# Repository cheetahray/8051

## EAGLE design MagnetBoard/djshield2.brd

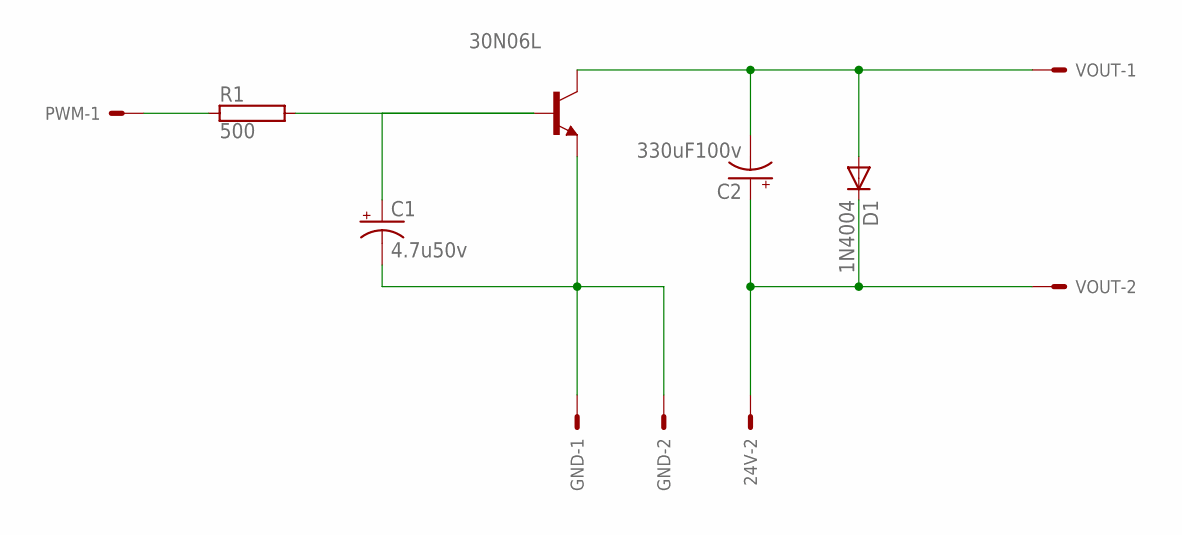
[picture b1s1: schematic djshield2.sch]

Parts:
24V: 87758-0216
30N06L: -NPN-TO126; TO126
C1: 4.7u50v; E1,8-4
C2: 330uF100v; E35-18
D1: 1N4004; DO41-10
GND: 87758-0216
PWM: 87758-0216
R1: 500; RS1/4
VOUT: 87758-0216

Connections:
unnamed: 30N06L.1 (E), C1.-, GND.1, GND.2
unnamed: 30N06L.2 (C), C2.-, D1.A, VOUT.1
unnamed: 24V.2, C2.+, D1.C, VOUT.2
unnamed: 30N06L.3 (B), C1.+, R1.2
unnamed: PWM.1, R1.1

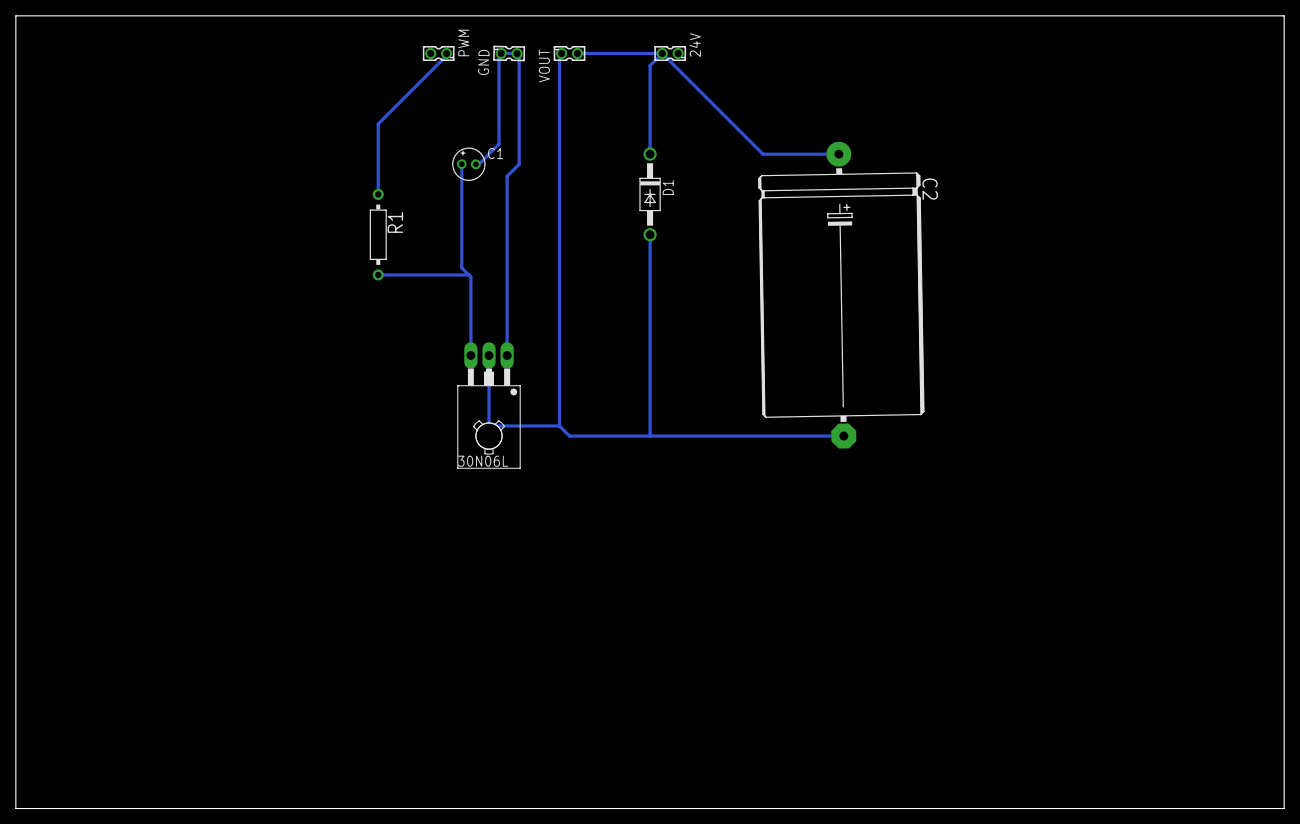
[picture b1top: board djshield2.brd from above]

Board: 2 copper layers, 160.0 x 100.0 mm, 9 parts (0 on the bottom side), 5 nets.

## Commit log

2013-03-04 音樂播不好 LCD會Busy當 LED到後半怪怪不亮 需要整個 memory 分析一次
2013-03-05 Midi parser 先這樣 Note 因為還沒線 所以沒辦法指定發 Noteoff (只有一個蜂鳴器)
2013-03-05 加入 Timer2
2013-03-06 加入 PWM 與 MUSIC 不能共用 因為同用 PCA 計數器 CR = 1, CR = 0
2013-03-07 加入軟體模擬PWM
2013-03-07 去掉Timer0中斷
2013-03-07 去掉 Timer0 中斷函數 partII
2013-03-08 去掉括號
2013-03-08 加入專案檔
2013-03-08 加入 midi through
2013-03-08 Enable uart2 and TX0
2013-03-08 1. 加電路圖 2. 加 uart2, 但是 rayCHANNEL = S2BUF 有問題，要等到74LS165接上才能真正測試
2013-03-09 uart1 與 uart2 互換 明天測試
2013-03-10 1. 電源電路 2. 74LS165 3. 測過 UART2 4. uart1 RI 一直會等於 1, 等測試
2013-03-10 改成74SL165N
2013-03-10 又改成SN74LS165@@
2013-03-11 uart1 跟 uart2 換回來 軟體 PWM 很有問題 @@ 電路圖畫到右邊排針
2013-03-12 1. 軟體 PWM 改成 Timer0 中斷 OK 2. 功率好像不夠? 3. 電路圖畫好了，還沒 Compiler 4. 若不好 Lay 可以 Feedback 改電路圖 5. 47 個空腳
2013-03-12 加入PCB
2013-03-12 加入 Autocad 檔
2013-03-12 Timer2 enable 敲木魚成功
2013-03-13 mcu layout 出不來 真是悲劇阿
2013-03-14 1. 換了 mpu, 結果 mcu 出來了線沒出來，昏倒 (然後他還有兩層@@) 2. 如果真的不行就換 IDE 了 3. 音樂與打鼓一起 4. 74LS165 Arduino 可以可是功率不夠? 8051 還是不行不知道是啥問題?
2013-03-15 74LS165電阻改成5.7K 快速敲鼓完成
2013-03-15 Channel 選擇器搞定
2013-03-16 打鼓三階段完成
2013-03-19 DEBUG搞定
2013-03-19 mcu 連線終於出來了 但是為什麼還沒有連排針的線呢
2013-03-19 新增FootPrint
2013-03-19 線終於好了嗚嗚嗚嗚
2013-03-23 PWM線性奶下垂
2013-03-25 軟體 PWM down 到 28Hz
2013-03-25 PWM done P1M1 = 0x02 連擊仍在設計中
2013-03-28 3060nl 暫時 OK
2013-03-28 加入電磁鐵
2013-03-31 今天music播不出來快搞死我了 結果是 TI = 0 的問題
2013-03-31 取消 midi out
2013-04-15 琴槌 x 2 鼓棒 x 1
2013-04-16 模仿和弦
2013-04-16 加 P00 ~ P04 五個西式木魚
2013-04-17 琴槌 鼓棒 木魚
2013-04-19 交響敲擊第一次測試OK
2013-04-19 竟然少一個 break
2013-04-23 調整琴槌速度
2013-04-24 加 6566676869
2013-04-25 木魚不夠力
2013-04-25 調個兩個墊片也壞兩個板還要重焊他x的
2013-04-26 調音結束
2013-04-29 板子可以work, 可是 Spec 差蠻多
2013-04-29 專案檔忘了放
2013-04-30 是可以敲拉，只是怪怪的
2013-04-30 我認輸，投降 (uart2 give up)
2013-05-02 旋轉 switch 搞定
2013-05-03 風鈴接近開關有問題
2013-05-03 接近開關有問題
2013-05-06 風鈴解決
2013-05-08 三角鐵解決
2013-05-14 channel 11 (12) 集合完成
2013-05-20 Oh~no~
2013-05-21 WTF...
2013-05-21 壓弦要比指播早
2013-05-22 擊毀一顆 P35 腳，我好難過 先測到這樣等實習生放慢節拍
2013-05-27 1. C和弦，速度80, 速度40 2. 壓力測試
2013-05-27 1. C和弦 2. 硬體 pwm 換至播弦
2013-05-28 1. 指播開關2 pitch 起始點 2. 壓力測試
2013-05-30 midi 板壓力測試
2013-05-30 把啟動移去pwm開動
2013-06-02 硬體 pwm 也納入控管
2013-06-04 今天先整理到此
2013-06-07 掰到吉他
2013-06-08 樂團初步完成 (鼓組分兩 channel)
2013-06-08 樂器初步 (鼓組到P6)
2013-06-09 和弦初步完成
2013-06-10 P14 被擊毀， QC 加入 P12 P13
2013-06-19 太多PWM起笑了
2013-06-19 P33 跳過
2013-06-22 鐵琴起笑退一版
2013-06-22 烏克分接OK
2013-06-23 程式：壓弦後撥弦的Delay 試著縮短 Velocity吉他收0
2013-06-25 01版第一版
2013-06-26 音都看過
2013-06-28 加入燈光
2013-06-28 1. 烏克 note off wrong 2. velocity 貌似 0 note off
2013-06-28 把吉他測keyboard加回去
2013-06-30 P14 input 竟然讀不到 用地雷 port P33 的 input
2013-07-01 脫褲字放屁改掉
2013-07-01 民謠吉他和弦 excel 表
2013-07-02 更動烏克麗麗和弦表
2013-07-02 放弦移去中斷 milestone
2013-07-02 烏克麗麗少一個
2013-07-02 取消民謠吉他 和弦/單音 兩個特別 note
2013-07-04 重 upload
2013-07-04 進度初步完成
2013-08-19 撥弦力道加大
2013-08-22 取消timer0
2013-09-11 改 Pedal Hihat
2013-09-11 Mosfet 快速測試
2014-08-11 差點找不到
2014-12-08 加 Organ Bike 到夢 2 板
2014-12-09 加入snare
2014-12-09 加 OrganBike excel table
2014-12-09 改 shanghai.c
2014-12-17 Organ Bike 少一個音
2014-12-18 改管風的 range 到 logic pro
2014-12-18 改 midi table
2014-12-18 move drumbool++ to release pitch
2015-07-20 開始畫 QFP64 7x7x0.4
